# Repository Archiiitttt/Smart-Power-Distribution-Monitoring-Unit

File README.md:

# Smart Power Distribution & Monitoring Unit ⚡

## 📖 Overview
This project is an industrial-grade **Power Distribution and Monitoring Unit** designed to manage high-voltage DC inputs (up to 40V) for robotic or automotive applications. 

Unlike standard power distribution boards, this unit features **active intelligent monitoring**. It is centered around an **STM32F103 (ARM Cortex-M3)** to sample current and temperature data, providing a hardware platform capable of proactive system shutdown before thermal runaway or over-current events occur.

### 🎯 Key Capabilities
* **Wide Input Range:** Designed to handle **12V–40V DC** input with dedicated surge protection.
* **Smart Protection:** Features **Reverse Polarity Protection** using a P-Channel MOSFET (IRF4905) to minimize voltage drop compared to traditional diode-based solutions.
* **High-Power Switching:** Capable of driving high-current external loads via an **IRFP4468 MOSFET** and a dedicated **TC4427 Gate Driver**.
* **Integrated Telemetry:** Supports power consumption monitoring via a **1mΩ Shunt + INA180 Amplifier** and thermal tracking through a **6-zone NTC matrix**.

---

## ⚙️ System Architecture
The hardware architecture is divided into four main functional stages: **Protection, Regulation, Control, and Actuation**.

### 1. Power Stage
* **Input Protection:** Includes an automotive blade fuse and TVS Diode (D3) to clamp voltage spikes.
* **Reverse Polarity:** Implemented via **IRF4905** (Q1) for high-efficiency protection.
* **Regulation Logic:** Two-stage step-down architecture:
    1.  **Buck Converter (U1 - LM2596S-ADJ):** Steps 40V down to 12V for the Gate Driver.
    2.  **LDO (U2 - AMS1117-3.3):** Steps 12V down to 3.3V for the MCU and sensor suite.

### 2. Control & Sensing
* **Microcontroller:** Powered by an **STM32F103C8Tx** (U5).
* **Current Monitoring:** High-side sensing using an **INA180A1** (U3) amplifier across a **1mΩ shunt resistor** (R10).
* **Thermal Monitoring:** Features **6x NTC Thermistors** (TH1-TH6) placed at critical points for system-wide temperature tracking.

---

## 🔌 Hardware Specifications

| Parameter | Value | Component |
| :--- | :--- | :--- |
| **Input Voltage** | 12V - 40V DC | XT60 / Terminal Block |
| **Logic Voltage** | 3.3V | AMS1117-3.3 |
| **Gate Drive Voltage** | 12V | TC4427VOA |
| **Main Switch** | 100V / 195A (Max) | IRFP4468PbF |
| **Current Sense** | High-Side, Analog | INA180 + 1mΩ Shunt |
| **Protection** | Reverse Polarity, Fuse, TVS | IRF4905, SMBJ43A |

---

## 🛠️ PCB Design (KiCad)
The PCB design focuses on high-current integrity and thermal management.

### Design Considerations:
* **Trace Width:** Critical high-current paths utilize **polygons and copper pours** to handle high amperage without excessive heat generation.
* **Thermal Management:** Integrated thermal vias under the LDO and MOSFETs to facilitate heat dissipation to the ground plane.
* **Noise Reduction:** Optimized placement of decoupling capacitors (C2, C3, C11) near the STM32 and high-speed driver pins to minimize switching noise.

---

## 📂 Repository Structure

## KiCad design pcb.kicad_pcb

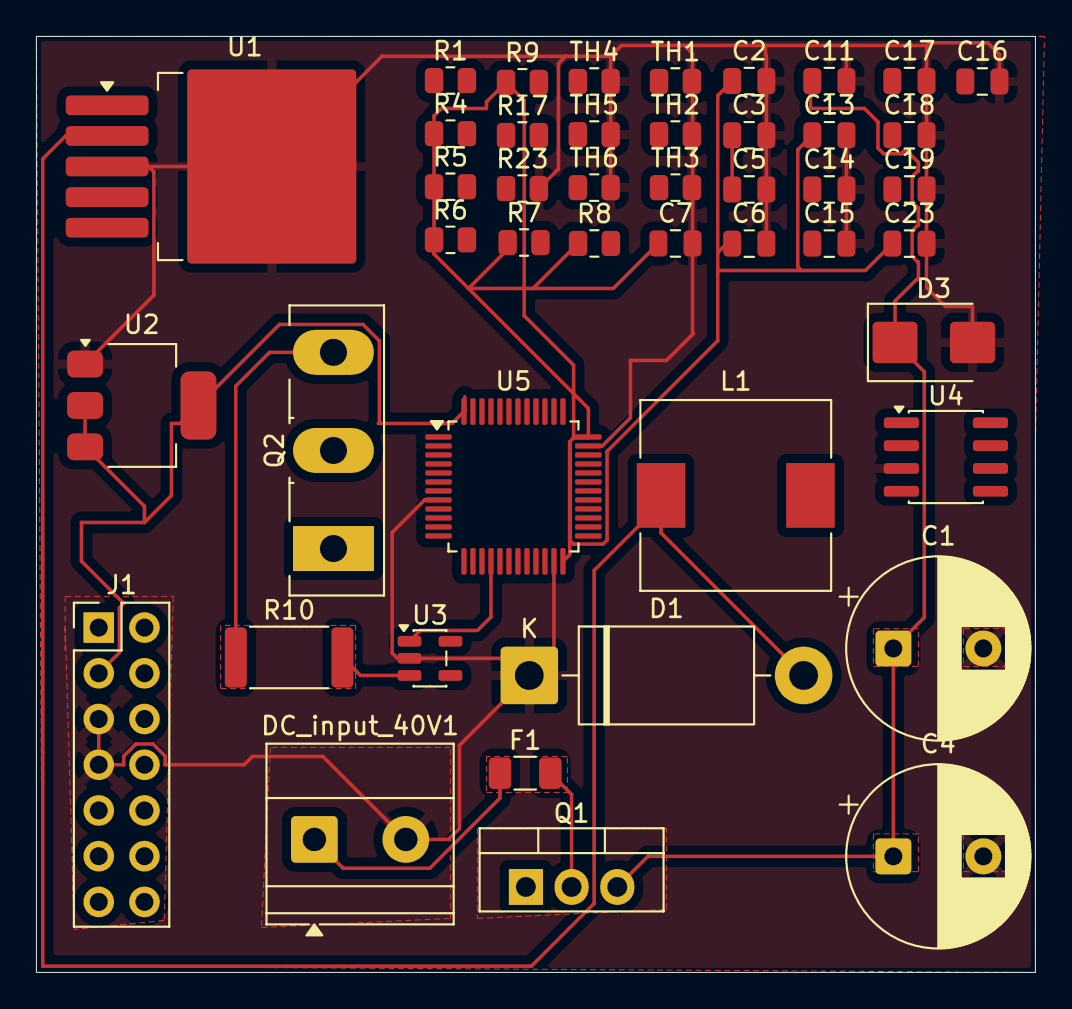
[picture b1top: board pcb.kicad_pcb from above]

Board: 2 copper layers, 55.5 x 52.0 mm, 45 parts (0 on the bottom side), 23 nets.

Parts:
C1: 470uf; CP_Radial_D10.0mm_P5.00mm
C2, C3, C7, C11, C13, C23: 0.1uf; C_0805_2012Metric
C4: 220uf; CP_Radial_D10.0mm_P5.00mm
C5: 330uf; C_0805_2012Metric
C6: 10uf; C_0805_2012Metric
C14, C15, C16, C17, C18, C19: 100nF; C_0805_2012Metric
D1: 1N5822; D_DO-201AD_P15.24mm_Horizontal
D3: D_TVS; D_SMB
DC_input_40V1: Conn_01x02; TerminalBlock_Phoenix_MKDS-1,5-2-5.08_1x02_P5.08mm_Horizont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
F1: Fuse_Small; Fuse_1206_3216Metric
J1: Conn_ST_STDC14; PinHeader_2x07_P2.54mm_Vertical
L1: 68uh; L_10.4x10.4_H4.8
Q1: IRF4905; TO-220-3_Vertical
Q2: IRFP4468PbF; TO-247-3_Vertical
R1, R4, R5, R6, R7, R8, R9: 10K; R_0805_2012Metric
R10: 1m; R_2512_6332Metric
R17: 10; R_0805_2012Metric
R23: 100K; R_0805_2012Metric
TH1, TH2, TH3, TH4, TH5, TH6: 10K; R_0805_2012Metric
U1: LM2596S-ADJ; TO-263-5_TabPin3
U2: AMS1117-3.3; SOT-223-3_TabPin2
U3: INA180A1; SOT-23-5
U4: TC4427xOA; SOIC-8_3.9x4.9mm_P1.27mm
U5: STM32F103C8Tx; LQFP-48_7x7mm_P0.5mm

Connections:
/+3V3: C2.1, C6.1, C7.1, C13.1, C23.1, J1.3 (VCC), R4.1, R5.1, R6.1, R7.1, R8.1, R9.1, U2.2 (VO), U2.3 (VI), U5.24 (VDD), U5.36 (VDD), U5.48 (VDD)
/+12V: C3.1, C5.1, L1.2, U4.6 (V_{DD})
GND: C1.2, C2.2, C3.2, C4.2, C5.2, C6.2, C7.2, C11.2, C13.2, C14.2, C15.2, C16.2, C17.2, C18.2, C19.2, C23.2, D1.1 (K), D3.2 (A2), DC_input_40V1.2, J1.5 (GND), J1.7 (GND), R23.2, TH1.2, TH2.2, TH3.2, TH4.2, TH5.2, TH6.2, U1.3 (GND), U2.1 (GND), U3.2 (GND), U4.3 (GND), U5.8 (VSSA), U5.23 (VSS), U5.35 (VSS), U5.47 (VSS)
unnamed: D1.2 (A), L1.1, U1.2 (OUT)
unnamed: C1.1, C4.1, C11.1, D3.1 (A1), Q1.3 (S), U1.1 (VIN)
unnamed: DC_input_40V1.1, F1.1
unnamed: J1.6 (JCLK/SWCLK), U5.3 (PC14)
unnamed: J1.4 (JTMS/SWDIO), U5.2 (PC13)
unnamed: J1.12 (~RST), R1.2
unnamed: F1.2, Q1.2 (D)
unnamed: Q2.1 (G), R17.2, R23.1
unnamed: Q2.3 (S), R10.1
unnamed: R10.2, U3.3 (+)
unnamed: U4.2 (IN_A), U5.29 (PA8)
unnamed: R17.1, U4.7 (OUT_A)
unnamed: R1.1, U5.7 (NRST)
unnamed: C14.1, R4.2, TH1.1, U5.10 (PA0)
unnamed: C15.1, R7.2, TH2.1, U5.11 (PA1)
unnamed: C17.1, R5.2, TH3.1, U5.12 (PA2)
unnamed: C18.1, R8.2, TH4.1, U5.13 (PA3)
unnamed: C16.1, R6.2, TH5.1, U5.14 (PA4)
unnamed: C19.1, R9.2, TH6.1, U5.15 (PA5)
unnamed: U3.1, U5.16 (PA6)

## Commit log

2026-02-09 Create Gerber Files
